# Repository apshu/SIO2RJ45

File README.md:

# SIO2RJ45
Converter PCB from Atari SIO to RJ45, with optional SIO2PC feature.

RJ45 is commonly used by Ethernet UTP cable

## Features
- STL files for housing
- SIO2PC function with optional USB to serial module
- Open-drain configuration for safe operation
- Separated +5V from SIO and USB. Allowing more power for RJ45 peripherals
- Audio, motor, Serial in/out and power are put to the Ethernet connector

## Folders

| Folder                          | Description                                          |
|---------------------------------|------------------------------------------------------|
| [PCB source](/PCB%20source/)    |  KiCAD Schematics and PCB files                      |
| [3D source](/3D%20source/)      |  Files for 3d casing                                 |
| [release](/release/)            |  Manufacturing files needed for building the project |

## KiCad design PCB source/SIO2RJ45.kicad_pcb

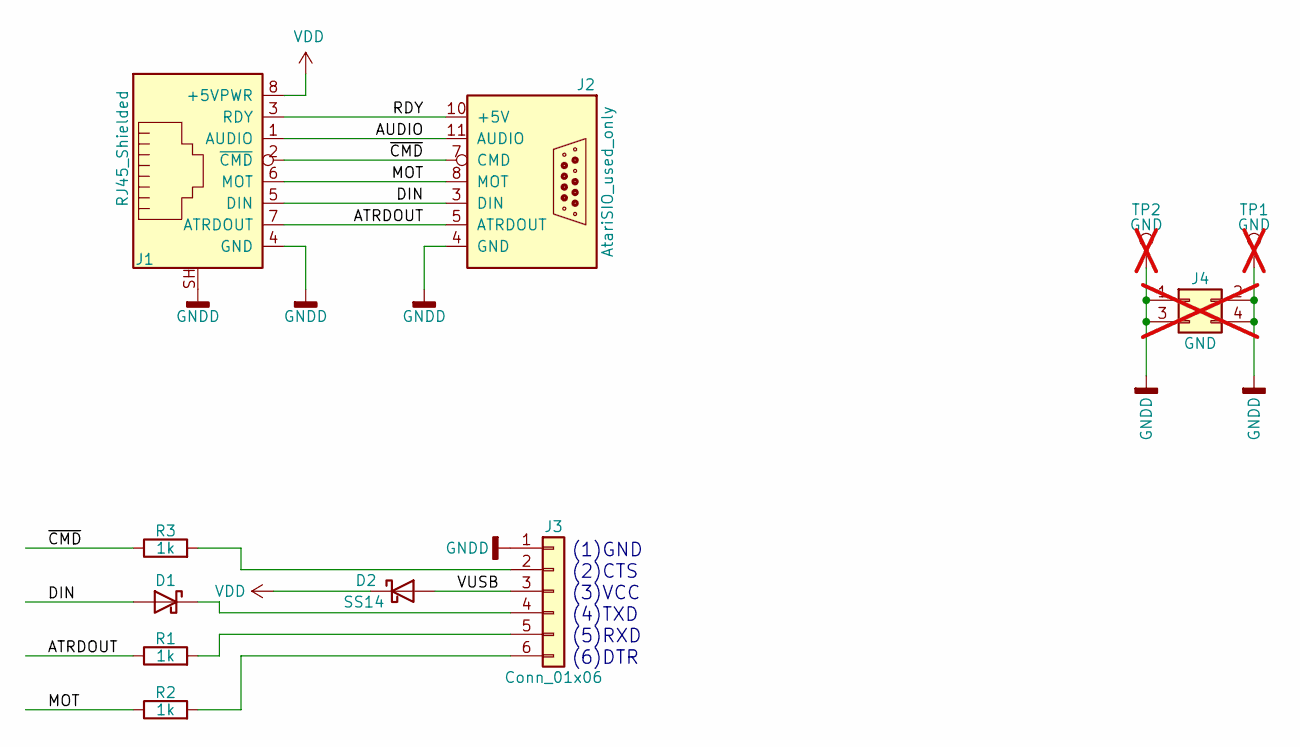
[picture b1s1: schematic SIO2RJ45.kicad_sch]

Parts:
D1: D_Schottky; D_A-405_P10.16mm_Horizontal
D2: SS14; D_SMA
J1: RJ45_Shielded; RJ45_Ninigi_GE
J2: AtariSIO_used_only; SIO_vertical_used_only
J3: Conn_01x06; PinHeader_1x06_P2.54mm_Vertical
J4: GND; PinHeader_2x02_P2.54mm_Vertical; not fitted
R1, R2, R3: 1k; R_0805_2012Metric_Pad1.20x1.40mm_HandSolder
TP1, TP2: GND; TestPoint_Loop_D2.60mm_Drill1.6mm_Beaded; not fitted

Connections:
/ATRDOUT: J1.7 (ATRDOUT), J2.5 (ATRDOUT), R1.1
/AUDIO: J1.1 (AUDIO), J2.11 (AUDIO)
/DIN: D1.2 (A), J1.5 (DIN), J2.3 (DIN)
/MOT: J1.6 (MOT), J2.8 (MOT), R2.1
/RDY: J1.3 (RDY), J2.10 (+5V)
/VUSB: D2.2 (A), J3.3
/~CMD: J1.2 (~CMD), J2.7 (CMD), R3.1
GNDD: J1.4 (GND), J1.SH, J2.4 (GND), J2.6 (GND), J3.1, J4.1, J4.2, J4.3, J4.4, TP1.1, TP2.1
unnamed: D1.1 (K), J3.4
unnamed: J3.2, R3.2
unnamed: J3.5, R1.2
unnamed: J3.6, R2.2
VDD: D2.1 (K), J1.8 (+5VPWR)

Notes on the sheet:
(1)GND (2)CTS (3)VCC (4)TXD (5)RXD (6)DTR

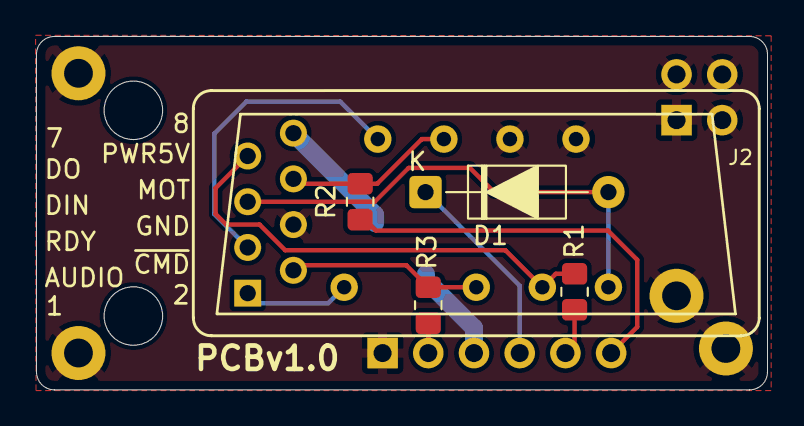
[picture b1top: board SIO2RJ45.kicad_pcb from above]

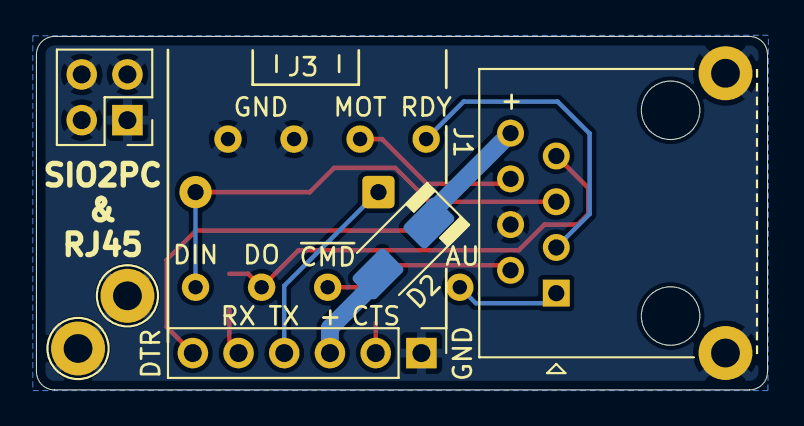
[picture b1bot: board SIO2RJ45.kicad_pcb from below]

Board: 2 copper layers, 40.6 x 19.6 mm, 11 parts (6 on the bottom side), 13 nets.

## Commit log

2025-06-13 Update README.md
    Improved README
2025-06-13 PCB files
2025-07-13 Housing 3D design and printable STL
2025-07-13 Typo in file name corrected
